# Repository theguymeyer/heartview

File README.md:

# Welcome to HeartView

A real-time testing system for pacemaker prototypes. 

The pacemaker project is a long standing challenge by Boston Scientific sponsored by McMaster University's Center for Software Certification -> [More](http://sqrl.mcmaster.ca/pacemaker.htm). This repo is the open-source (GPLv3) code base for the HeartView Testing GUI, embedded development files, and design files for the hardware and electrical systems. Even more info [here](https://guymeyer.me/project/heartview).

## Directory

HeartView Documentation -> https://github.com/theguymeyer/heartview/blob/master/course_dev/documentation/heartview_explained/intro_to_heartview.pdf

MacOS Executeable for HeartView -> https://github.com/theguymeyer/heartview/tree/master/course_dev/ui-HeartView/mac/exe

Windows Executeable for HeartView -> https://github.com/theguymeyer/heartview/tree/master/course_dev/ui-HeartView/win/exe

Nucleo Embedded Codebase -> https://github.com/theguymeyer/heartview/tree/master/course_dev/shield_nucleo_rev0/CubeMX

PCB Build Packages -> https://github.com/theguymeyer/heartview/tree/master/course_dev/Production/build

Heart Shield Design (Nucleo) -> https://github.com/theguymeyer/heartview/tree/master/course_dev/shield_nucleo_rev0

Pacemaker Shield Design -> https://github.com/theguymeyer/heartview/tree/master/course_dev/shield_pacemaker

Mechanical Design (casing) -> https://github.com/theguymeyer/heartview/tree/master/course_dev/casing/rev0

Testing Files -> https://github.com/theguymeyer/heartview/tree/master/course_dev/testing

## How to get involved

We invite you to contribute and help build a robust way to learn about pacemakers in a fun and engaging way. Reach out to the McSCert Research Group at McMaster Univeristy or get in touch view GitHub.

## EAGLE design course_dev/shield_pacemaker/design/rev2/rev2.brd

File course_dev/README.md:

# Pacemaker Project with Dedicated Testing System

TODO

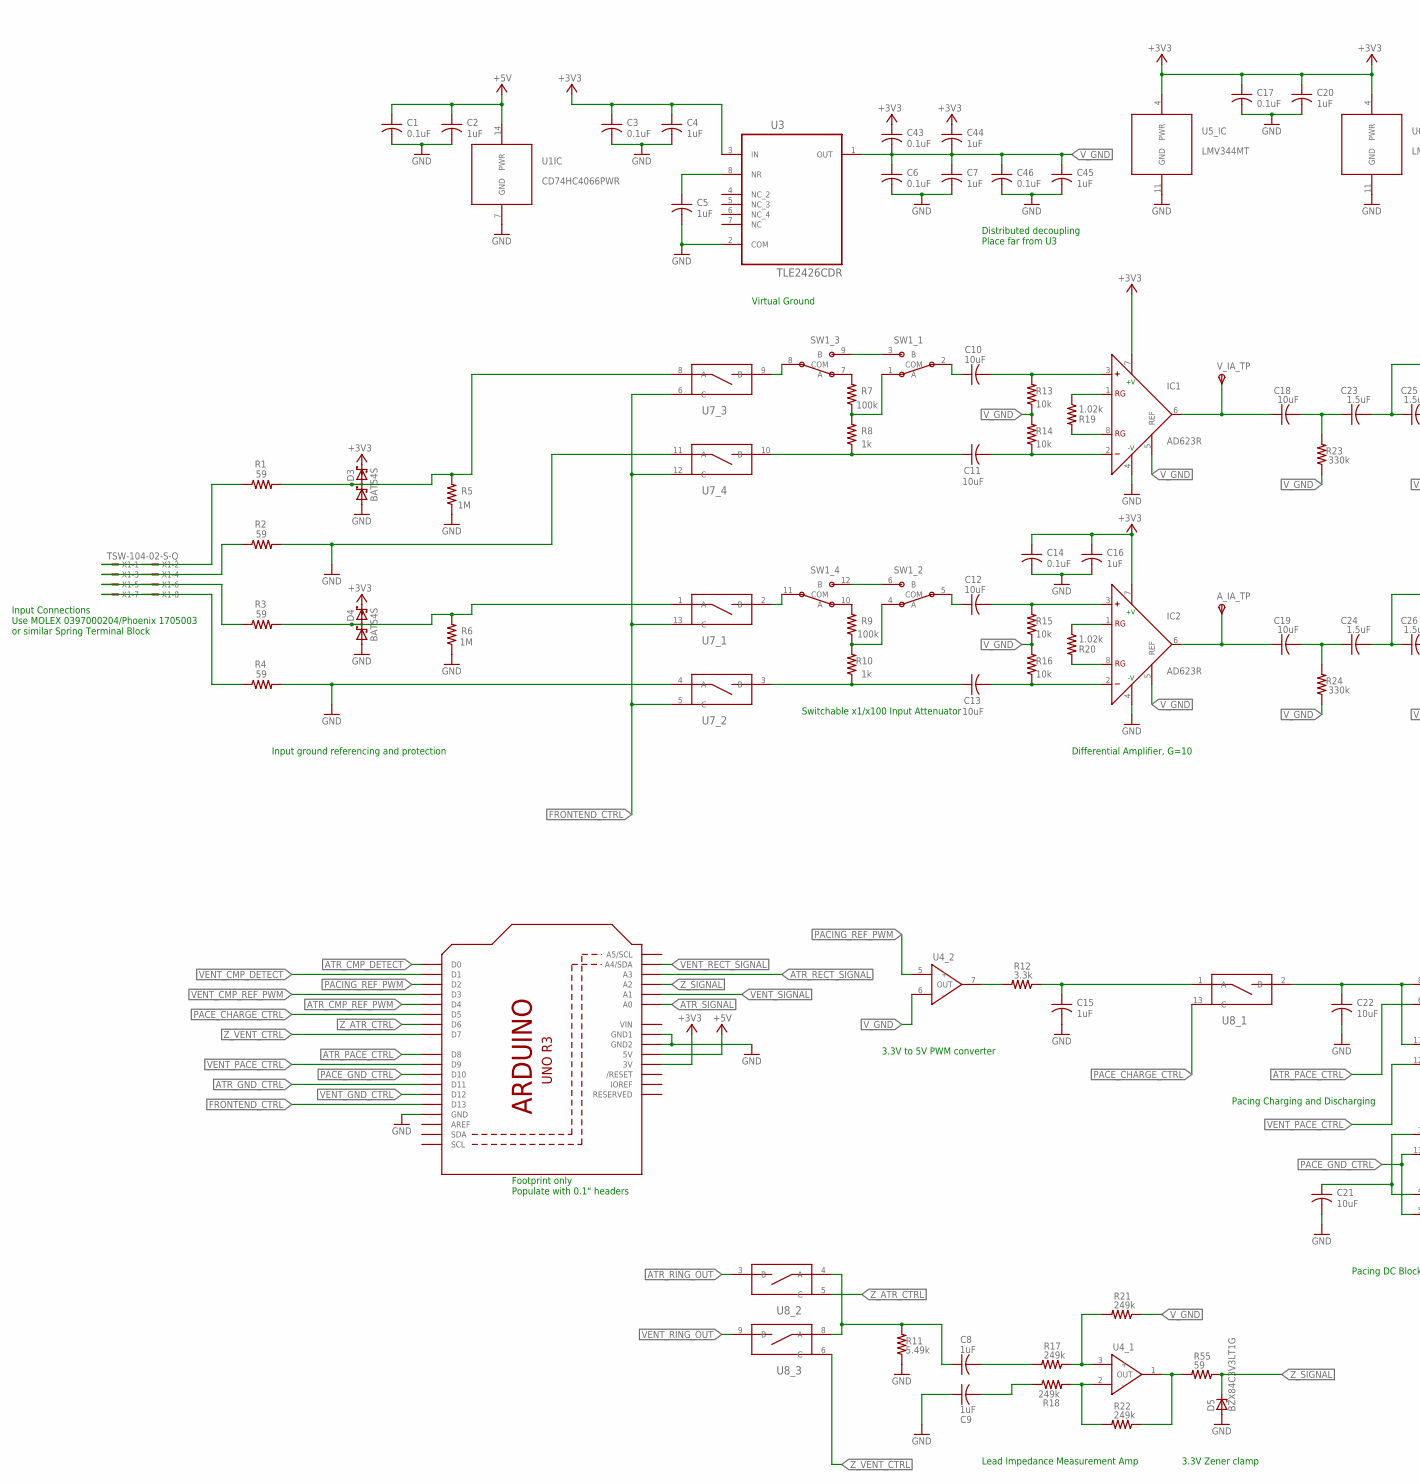
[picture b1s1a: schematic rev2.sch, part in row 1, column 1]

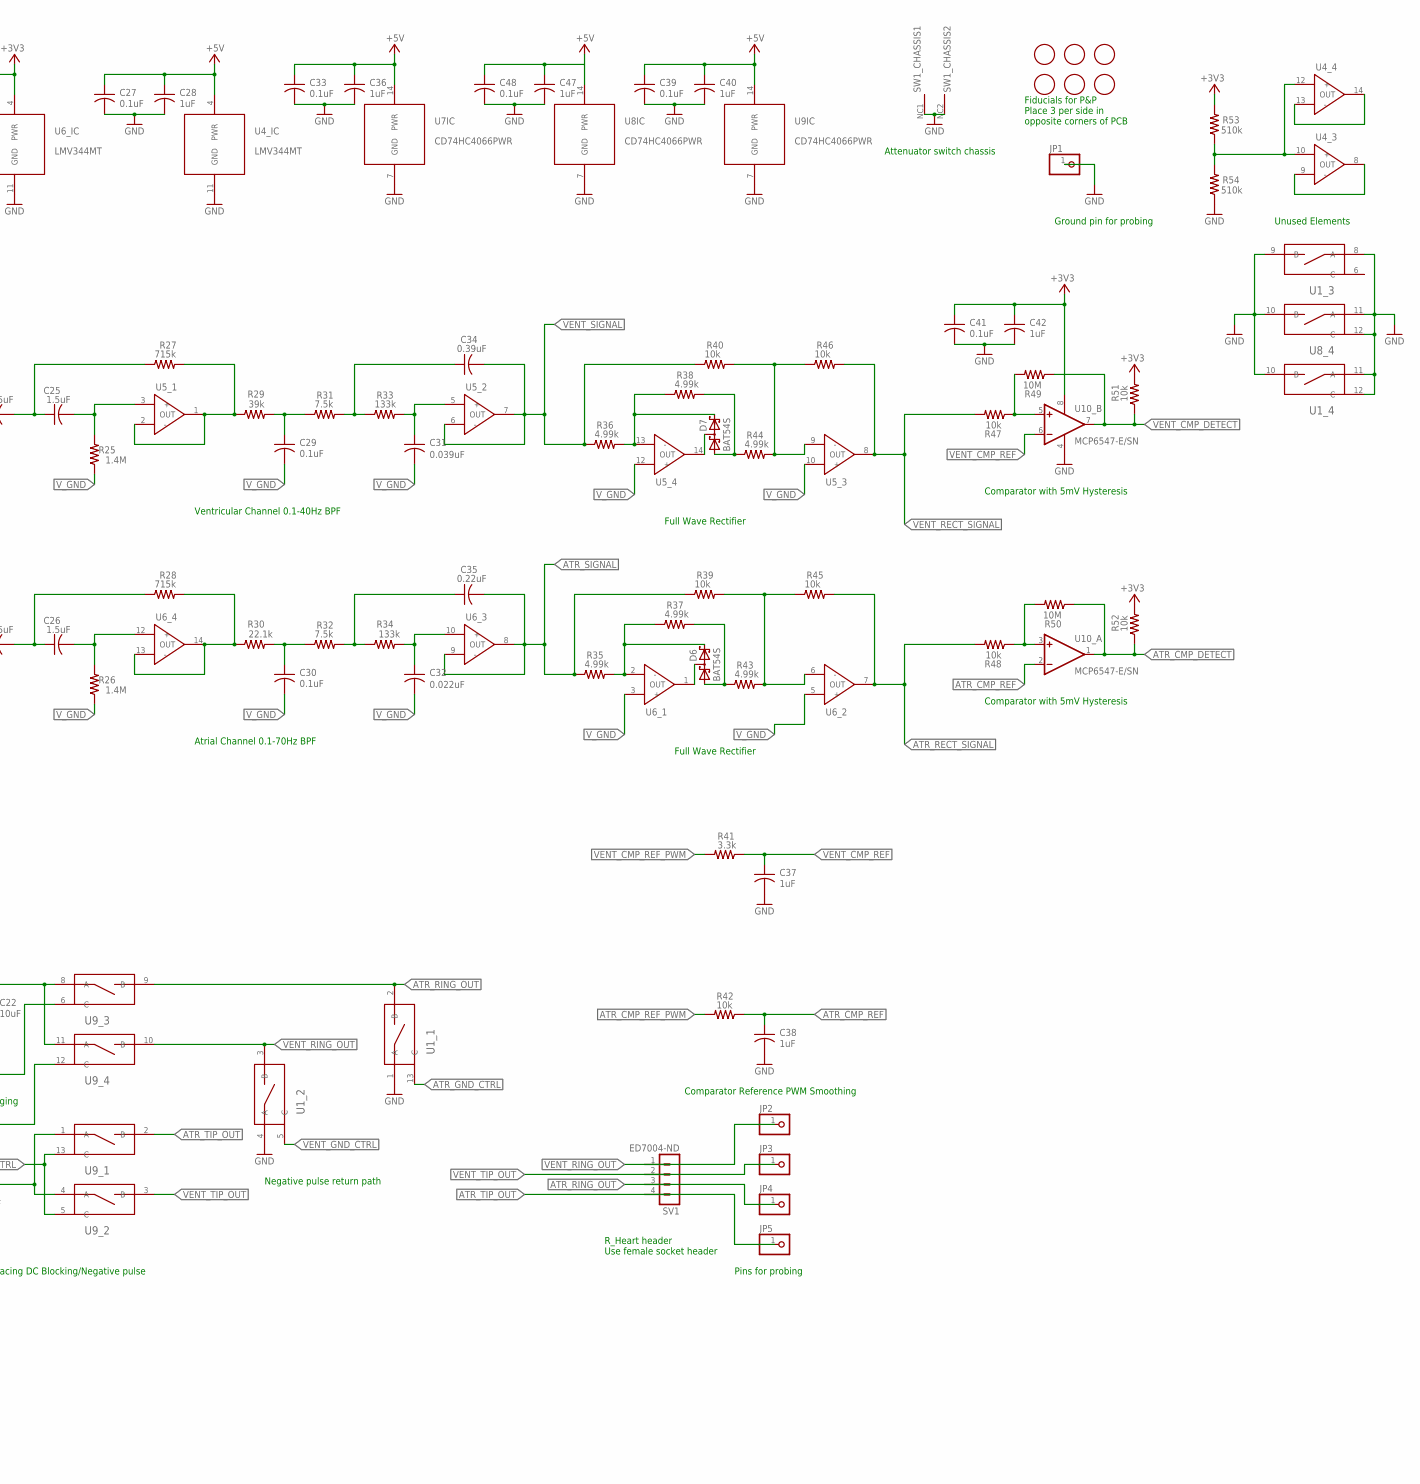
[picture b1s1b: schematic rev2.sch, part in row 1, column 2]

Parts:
A_IA_TP: TPSTP06R; TP06R
C1, C3, C6, C14, C17, C27, C29, C30, C33, C39, C41, C43, C46, C48: 0.1uF; C0805
C2, C4, C5, C7, C8, C9, C15, C16, C20, C28, C36, C37, C38, C40, C42, C44, C45, C47: 1uF; C0805
C10, C11, C12, C13, C18, C19, C21, C22: 10uF; C0805
C23, C24, C25, C26: 1.5uF; C0805
C31: 0.039uF; C0805
C32: 0.022uF; C0805
C34: 0.39uF; C0805
C35: 0.22uF; C0805
D3, D4, D6, D7: BAT54S; SOT23
D5: BZX84C3V3LT1G; SOT23
IC1, IC2: AD623R; SO8
JP1, JP2, JP3, JP4, JP5: PINHD-1X1; 1X01
R1, R2, R3, R4, R55: 59; R0805
R5, R6: 1M; R0805
R7, R9: 100k; R0805
R8, R10: 1k; R0805
R11: 5.49k; R0805
R12, R41: 3.3k; R0805
R13, R14, R15, R16, R39, R40, R42, R45, R46, R47, R48, R51, R52: 10k; R0805
R17, R18, R21, R22: 249k; R0805
R19, R20: 1.02k; R0805
R23, R24: 330k; R0805
R25, R26: 1.4M; R0805
R27, R28: 715k; R0805
R29: 39k; R0805
R30: 22.1k; R0805
R31, R32: 7.5k; R0805
R33, R34: 133k; R0805
R35, R36, R37, R38, R43, R44: 4.99k; R0805
R49, R50: 10M; R0805
R53, R54: 510k; R0805
SV1: ED7004-ND; MA04-1
SW1: EG4208; EG4208-PACKAGE
U1, U7, U8, U9: CD74HC4066PWR; SOP65P640X110-14N
U2: ARDUINOR3-DIMENSION; ARDUINOR3
U3: TLE2426CDR; SOIC127P600X175-8N
U4, U5, U6: LMV344MT; SOP65P640X110-14N
U10: MCP6547-E/SN; SOIC127P600X175-8N
U$1, U$2, U$3, U$4, U$5, U$6: FIDUCIAL; FIDUCIAL_1MM
V_IA_TP: TPSTP06R; TP06R
X1: TSW-104-02-S-Q

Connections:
+3V3: C3.1, C4.1, C14.1, C16.1, C17.1, C20.1, C41.1, C42.1, C43.1, C44.1, D3.2 (C2), D4.2 (C2), IC1.7 (+V), IC2.7 (+V), R51.2, R52.2, R53.2, U2.3V, U3.3 (IN), U5.4 (PWR), U6.4 (PWR), U10.8 (V+)
+5V: C1.1, C2.1, C27.1, C28.1, C33.1, C36.1, C39.1, C40.1, C47.1, C48.1, U1.14 (PWR), U2.5V, U4.4 (PWR), U7.14 (PWR), U8.14 (PWR), U9.14 (PWR)
ATR_CMP_DETECT: R50.1, R52.1, U2.D0, U10.1 (OUT)
ATR_CMP_REF: C38.1, R42.1, U10.2 (-IN)
ATR_CMP_REF_PWM: R42.2, U2.D4
ATR_GND_CTRL: U1.13 (C), U2.D11
ATR_PACE_CTRL: U2.D8, U9.6 (C)
ATR_RECT_SIGNAL: R45.2, R48.2, U2.A3, U6.7 (OUT)
ATR_RING: D4.3 (C1A2), R3.2, R6.2, U7.1 (A)
ATR_RING_OUT: JP4.1, SV1.3, U1.2 (B), U8.3 (B), U9.9 (B)
ATR_SIGNAL: C35.2, R35.1, R39.1, U2.A0, U6.8 (OUT), U6.9 (-)
ATR_TIP_OUT: JP5.1, SV1.4, U9.2 (B)
FRONTEND_CTRL: U2.D13, U7.5 (C), U7.6 (C), U7.12 (C), U7.13 (C)
GND: C1.2, C2.2, C3.2, C4.2, C5.2, C6.2, C7.2, C9.1, C14.2, C15.2, C16.2, C17.2, C20.2, C21.2, C22.2, C27.2, C28.2, C33.2, C36.2, C37.2, C38.2, C39.2, C40.2, C41.2, C42.2, C45.2, C46.2, C47.2, C48.2, D3.1 (A1), D4.1 (A1), D5.1 (A), IC1.4 (-V), IC2.4 (-V), JP1.1, R2.2, R4.2, R5.1, R6.1, R11.1, R54.1, SW1.NC1 (V-), SW1.NC2 (V-), U1.1 (A), U1.4 (A), U1.7 (GND), U1.8 (A), U1.9 (B), U1.10 (B), U1.11 (A), U1.12 (C), U2.GND, U2.GND1, U2.GND2, U3.2 (COM), U4.11 (GND), U5.11 (GND), U6.11 (GND), U7.4 (A), U7.7 (GND), U7.11 (A), U8.7 (GND), U8.10 (B), U8.11 (A), U8.12 (C), U9.7 (GND), U10.4 (V-)
unnamed: C10.2, IC1.3 (+), R13.2
unnamed: C11.2, IC1.2 (-), R14.1
unnamed: C18.1, IC1.6 (OUT), V_IA_TP.TP
unnamed: IC1.1 (RG), R19.1
unnamed: R7.2, SW1.7 (A)
unnamed: C18.2, C23.1, R23.2
unnamed: C23.2, C25.1, R27.1
unnamed: C11.1, R8.1, U7.10 (B)
unnamed: C13.2, IC2.2 (-), R16.1
unnamed: C29.1, R29.2, R31.1
unnamed: C34.1, R31.2, R33.1
unnamed: C13.1, R10.1, U7.3 (B)
unnamed: D6.2 (C2), R35.2, R37.1, U6.2 (-)
unnamed: R9.2, SW1.10 (A)
unnamed: IC2.1 (RG), R20.1
unnamed: IC2.8 (RG), R20.2
unnamed: C19.2, C24.1, R24.2
unnamed: D6.3 (C1A2), U6.1 (OUT)
unnamed: IC1.8 (RG), R19.2
unnamed: C12.2, IC2.3 (+), R15.2
unnamed: C15.1, R12.1, U8.1 (A)
unnamed: C21.1, U9.1 (A), U9.4 (A)
unnamed: R22.1, R55.2, U4.1 (OUT)
unnamed: D7.3 (C1A2), U5.14 (OUT)
unnamed: R28.2, R30.1, U6.13 (-), U6.14 (OUT)
unnamed: SW1.6 (B), SW1.12 (B)
unnamed: C24.2, C26.1, R28.1
unnamed: C22.1, U8.2 (B), U9.8 (A), U9.11 (A)
unnamed: C25.2, R25.2, U5.3 (+)
unnamed: R27.2, R29.1, U5.1 (OUT), U5.2 (-)
unnamed: C5.1, U3.8 (NR)
unnamed: C31.1, R33.2, U5.5 (+)
unnamed: C30.1, R30.2, R32.1
unnamed: R48.1, R50.2, U10.3 (+IN)
unnamed: C35.1, R32.2, R34.1
unnamed: D6.1 (A1), R37.2, R43.1
unnamed: C26.2, R26.2, U6.12 (+)
unnamed: R47.1, R49.2, U10.5 (+IN)
unnamed: C32.1, R34.2, U6.10 (+)
unnamed: R39.2, R43.2, R45.1, U6.6 (-)
unnamed: SW1.3 (B), SW1.9 (B)
unnamed: C8.1, R11.2, U8.4 (A), U8.8 (A)
unnamed: A_IA_TP.TP, C19.1, IC2.6 (OUT)
unnamed: U4.8 (OUT), U4.9 (-)
unnamed: R12.2, U4.7 (OUT)
unnamed: R17.1, R21.2, U4.3 (+)
unnamed: R18.2, R22.2, U4.2 (-)
unnamed: C9.2, R18.1
unnamed: C8.2, R17.2
unnamed: U4.13 (-), U4.14 (OUT)
unnamed: R53.1, R54.2, U4.10 (+), U4.12 (+)
unnamed: R4.1, X1.7, X1.8
unnamed: R2.1, X1.3, X1.4
unnamed: R3.1, X1.5, X1.6
unnamed: R7.1, R8.2, SW1.1 (A)
unnamed: R1.1, X1.1, X1.2
unnamed: SW1.8 (COM), U7.9 (B)
unnamed: SW1.11 (COM), U7.2 (B)
unnamed: R9.1, R10.2, SW1.4 (A)
unnamed: D7.2 (C2), R36.2, R38.1, U5.13 (-)
unnamed: C12.1, SW1.5 (COM)
unnamed: C10.1, SW1.2 (COM)
unnamed: D7.1 (A1), R38.2, R44.1
unnamed: R40.2, R44.2, R46.1, U5.9 (-)
PACE_CHARGE_CTRL: U2.D5, U8.13 (C)
PACE_GND_CTRL: U2.D10, U9.5 (C), U9.13 (C)
PACING_REF_PWM: U2.D2, U4.5 (+)
VENT_CMP_DETECT: R49.1, R51.1, U2.D1, U10.7 (OUT)
VENT_CMP_REF: C37.1, R41.1, U10.6 (-IN)
VENT_CMP_REF_PWM: R41.2, U2.D3
VENT_GND_CTRL: U1.5 (C), U2.D12
VENT_PACE_CTRL: U2.D9, U9.12 (C)
VENT_RECT_SIGNAL: R46.2, R47.2, U2.A4 (A4/SDA), U5.8 (OUT)
VENT_RING: D3.3 (C1A2), R1.2, R5.2, U7.8 (A)
VENT_RING_OUT: JP2.1, SV1.1, U1.3 (B), U8.9 (B), U9.10 (B)
VENT_SIGNAL: C34.2, R36.1, R40.1, U2.A1, U5.6 (-), U5.7 (OUT)
VENT_TIP_OUT: JP3.1, SV1.2, U9.3 (B)
VIN: U2.VIN
V_GND: C6.1, C7.1, C29.2, C30.2, C31.2, C32.2, C43.2, C44.2, C45.1, C46.1, IC1.5 (REF), IC2.5 (REF), R13.1, R14.2, R15.1, R16.2, R21.1, R23.1, R24.1, R25.1, R26.1, U3.1 (OUT), U4.6 (-), U5.10 (+), U5.12 (+), U6.3 (+), U6.5 (+)
Z_ATR_CTRL: U2.D6, U8.5 (C)
Z_SIGNAL: D5.3 (C), R55.1, U2.A2
Z_VENT_CTRL: U2.D7, U8.6 (C)

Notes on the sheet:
Ventricular Channel 0.1-40Hz BPF
Atrial Channel 0.1-70Hz BPF
Pacing Charging and Discharging
Unused Elements
Lead Impedance Measurement Amp
Pacing DC Blocking/Negative pulse
Comparator with 5mV Hysteresis
Comparator Reference PWM Smoothing
Footprint only Populate with 0.1" headers
Differential Amplifier, G=10
3.3V to 5V PWM converter
Input ground referencing and protection
Switchable x1/x100 Input Attenuator
R_Heart header Use female socket header
Negative pulse return path
Full Wave Rectifier
Virtual Ground
Distributed decoupling Place far from U3
Input Connections Use MOLEX 0397000204/Phoenix 1705003 or similar Spring Terminal Block
Pins for probing
Fiducials for P&P Place 3 per side in opposite corners of PCB
Ground pin for probing
Attenuator switch chassis
3.3V Zener clamp

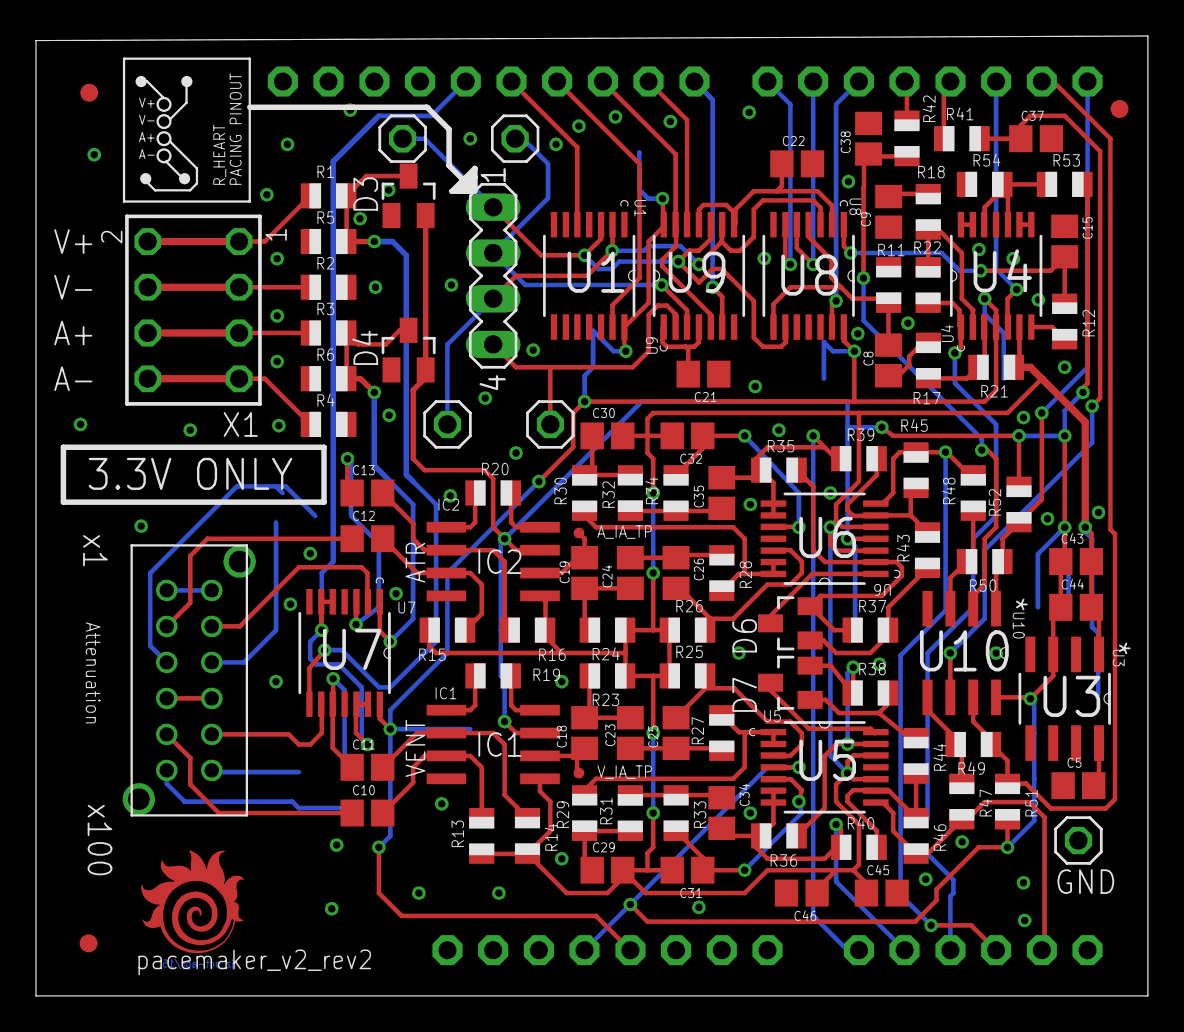
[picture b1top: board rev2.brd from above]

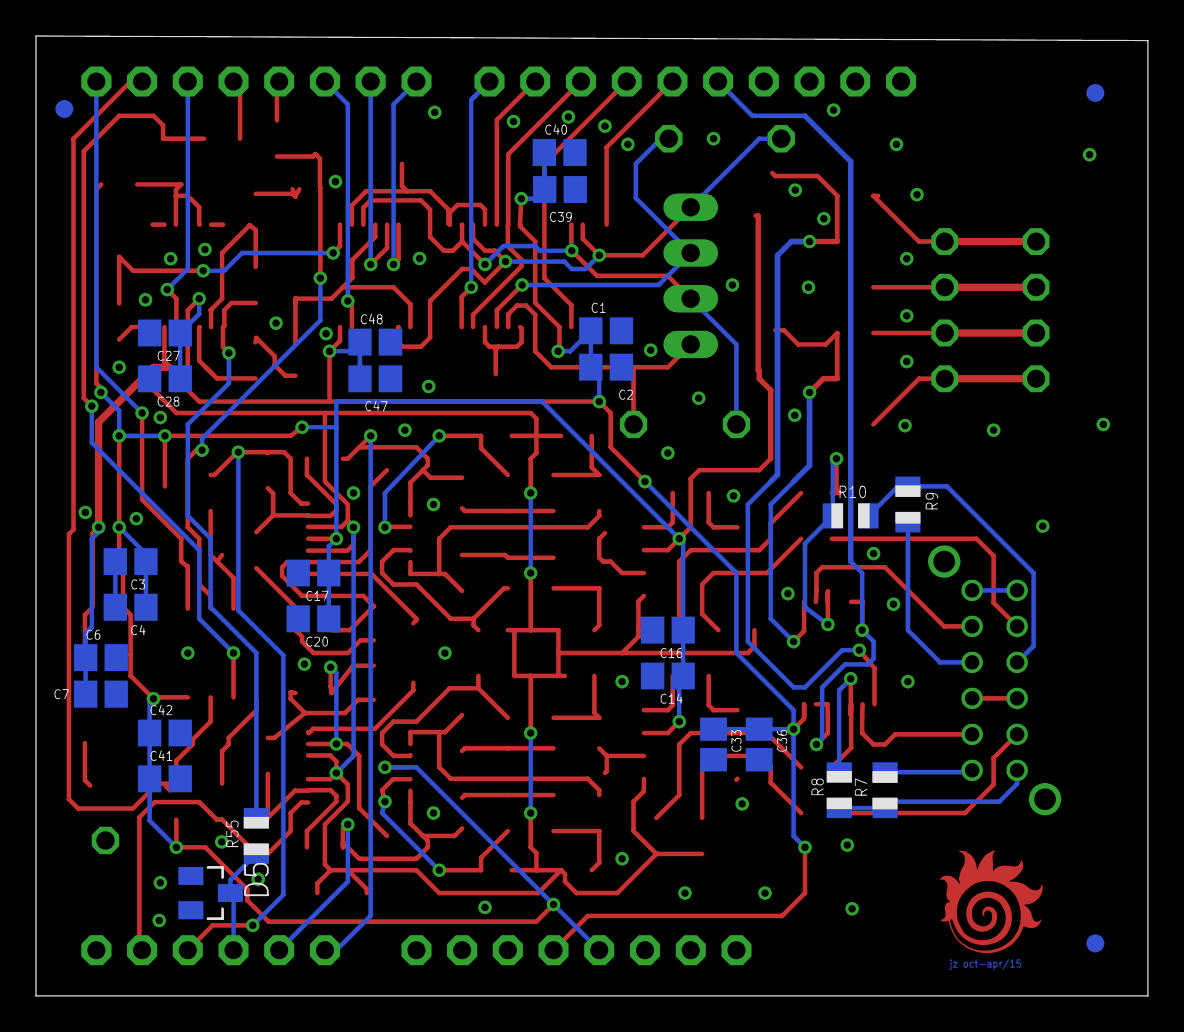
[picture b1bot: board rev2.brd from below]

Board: 2 copper layers, 61.8 x 53.3 mm, 137 parts (29 on the bottom side), 95 nets.

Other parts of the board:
U$7: FIREBALL

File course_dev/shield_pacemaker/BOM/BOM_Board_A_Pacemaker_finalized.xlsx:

BOM - Board A (Pacemaker)
# | Designator | Quantity | Comment | Value | Footprint | Description | Manufacturer | Price | Total Price
1 | C32 | 1 | CAP CER 0.022UF 50V X7R 0805 | C0805C223K5RACTU | 0805 | SMD/SMT 50V 0.022uF X7R 0805 10% | KEMET | 0.15 | 0.15
2 | C31 | 1 | CAP CER 0.039UF 50V X7R 0805 | C0805C393K5RACTU | 0805 | SMD/SMT 50V 0.039uF X7R 0805 10% | KEMET | 0.34 | 0.34
3 | C1, C3, C6, C14, C17, C27, C29, C30, C33, C39, C41, C43, C46, C48 | 14 | CAP CER 0.1UF 50V X7R 0805 | C0805C104J5RACTU | 0805 | SMD/SMT 50V 0.1uF X7R 0805 5% | KEMET | 0.195 | 2.73
4 | C35 | 1 | CAP CER 0.22UF 16V X7R 0805 | C0805C224K4RACTU | 0805 | SMD/SMT 16V 0.22uF X7R 0805 10% | KEMET | 0.3 | 0.3
5 | C34 | 1 | CAP CER 0.39UF 50V X7R 0805 | C0805X394K5RACTU | 0805 | SMD/SMT 50V 0.39uF X7R 0805 10% | KEMET | 0.98 | 0.98
6 | R19, R20 | 2 | RES SMD 1.02K OHM 1% 1/8W 0805 | ERJ-6ENF1021V | 0805 | SMD 0805 1.02Kohms 1% | Panasonic Electronic Components | 0.16 | 0.32
7 | R25, R26 | 2 | RES SMD 1.4M OHM 1% 1/8W 0805 | ERJ-6ENF1404V | 0805 | SMD 0805 1.4Mohms 1% | Panasonic Electronic Components | 0.16 | 0.32
8 | C23, C24, C25, C26 | 4 | CAP CER 1.5UF 50V X7R 0805 | C2012X7R1H155K125AC | 0805 | SMD/SMT 0805 50V 1.5uF X7R 10% | TDK Corporation | 1.09 | 4.36
9 | R7, R9 | 2 | RES SMD 100K OHM 1% 1/8W 0805 | ERJ-6ENF1003V | 0805 | SMD 0805 100Kohms 1% | Panasonic Electronic Components | 0.16 | 0.32
10 | R49, R50 | 2 | RES SMD 10M OHM 1% 1/8W 0805 | CRCW080510M0FKEB | 0805 | SMD 1/8watt 10Mohms 1% | Vishay Dale | 0.16 | 0.32
11 | R13, R14, R15, R16, R39, R40, R42, R45, R46, R47, R48, R51, R52 | 13 | RES SMD 10K OHM 1% 1/8W 0805 | ERJ-6ENF1002V | 0805 | SMD 0805 10Kohms 1% | Panasonic Electronic Components | 0.114 | 1.482
12 | C10, C11, C12, C13, C18, C19, C21, C22 | 8 | CAP CER 10UF 10V X5R 0805 | CL21A106KPFNNWE | 0805 | SMD/SMT 10V 10uF X7R 0805 10% | Samsung Electro-Mechanics | 0.27 | 2.16
13 | R33, R34 | 2 | RES SMD 133K OHM 1% 1/8W 0805 | ERJ-6ENF1333V | 0805 | SMD 0805 133Kohms 1% | Panasonic Electronic Components | 0.16 | 0.32
14 | R5, R6 | 2 | RES SMD 1M OHM 1% 1/8W 0805 | ERJ-6ENF1004V | 0805 | SMD 0805 1Mohms 1% Tol | Panasonic Electronic Components | 0.16 | 0.32
15 | R8, R10 | 2 | RES SMD 1K OHM 1% 1/8W 0805 | ERJ-6ENF1001V | 0805 | SMD 0805 1Kohms 1% | Panasonic Electronic Components | 0.16 | 0.32
16 | C2, C4, C5, C7, C8, C9, C15, C16, C20, C28, C36, C37, C38, C40, C42, C44, C45, 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 | 18 | CAP CER 1UF 16V X5R 0805 | C0805C105K4PACTU | 0805 | SMD/SMT 16V 1uF X5R 0805 10% | KEMET | 0.231 | 4.158
17 | R30 | 1 | RES SMD 22.1K OHM 1% 1/8W 0805 | ERJ-6ENF2212V | 0805 | SMD 0805 22.1Kohms 1% | Panasonic Electronic Components | 0.16 | 0.16
18 | R17, R18, R21, R22 | 4 | RES SMD 249K OHM 1% 1/8W 0805 | ERJ-6ENF2493V | 0805 | SMD 0805 249Kohms 1% | Panasonic Electronic Components | 0.16 | 0.64
19 | R12, R41 | 2 | RES SMD 3.3K OHM 1% 1/8W 0805 | ERJ-6ENF3301V | 0805 | SMD 0805 3.3Kohms 1% | Panasonic Electronic Components | 0.16 | 0.32
20 | R23, R24 | 2 | RES SMD 330K OHM 1% 1/8W 0805 | ERJ-6ENF3303V | 0805 | SMD 0805 330Kohms 1% | Panasonic Electronic Components | 0.16 | 0.32
21 | R29 | 1 | RES SMD 39K OHM 1% 1/8W 0805 | ERJ-6ENF3902V | 0805 | SMD 0805 39Kohms 1% | Panasonic Electronic Components | 0.16 | 0.16
22 | R35, R36, R37, R38, R43, R44 | 6 | RES SMD 4.99K OHM 1% 1/8W 0805 | ERJ-6ENF4991V | 0805 | SMD 0805 4.99Kohms 1% | Panasonic Electronic Components | 0.16 | 0.96
23 | R11 | 1 | RES SMD 5.49K OHM 1% 1/8W 0805 | ERJ-6ENF5491V | 0805 | SMD 0805 5.49Kohms 1% | Panasonic Electronic Components | 0.16 | 0.16
24 | R53, R54 | 2 | RES SMD 510K OHM 1% 1/8W 0805 | ERJ-6ENF5103V | 0805 | SMD 0805 510Kohms 1% | Panasonic Electronic Components | 0.16 | 0.32
25 | R1, R2, R3, R4, R55 | 5 | RES SMD 59 OHM 1% 1/8W 0805 | ERJ-6ENF59R0V | 0805 | SMD 0805 59.0ohms 1% Tol | Panasonic Electronic Components | 0.16 | 0.8
26 | R31, R32 | 2 | RES SMD 7.5K OHM 1% 1/8W 0805 | ERJ-6ENF7501V | 0805 | SMD 0805 7.5Kohms 1% | Panasonic Electronic Components | 0.16 | 0.32
27 | R27, R28 | 2 | RES SMD 715K OHM 1% 1/8W 0805 | ERJ-6ENF7153V | 0805 | SMD 0805 715Kohms 1% | Panasonic Electronic Components | 0.16 | 0.32
28 | D3, D4, D6, D7 | 4 | DIODE ARRAY SCHOTTKY 30V SOT23 | BAT54S,215 | SOT-23-3 | SCHOTTKY 30V DUAL | Nexperia USA Inc. | 0.21 | 0.84
29 | D5 | 1 | DIODE ZENER 3.3V 225MW SOT23-3 | BZX84C3V3LT1G | SOT-23-3 | DIODE ZENER 3.3V 225MW SOT23-3 | ON Semiconductor | 0.19 | 0.19
30 | U1, U7, U8, U9 | 4 | IC SWITCH QUAD 1X2 14TSSOP | CD74HC4066PWR | TSSOP-14 | IC SWITCH QUAD 1X2 14TSSOP | Texas Instruments | 0.86 | 3.44
31 | SW1 | 1 | SWITCH SLIDE 4PDT 200MA 30V | EG4208 |  | SWITCH SLIDE 4PDT 200MA 30V | E-Switch | 1.95 | 1.95
32 | U4, U5, U6 | 3 | IC OPAMP GP 4 CIRCUIT 14TSSOP | LMV774MT/NOPB | TSSOP-14 | IC OPAMP GP 4 CIRCUIT 14TSSOP | Texas Instruments | 4.45 | 13.35
33 | U10 | 1 | IC COMP 1.6V DUAL O-D 8SOIC | MCP6547-E/SN | SOIC-8 | IC COMP 1.6V DUAL O-D 8SOIC | Microchip Technology | 0.91 | 0.91
34 | U3 | 1 | IC VREF GND REF 20V 1% 8SOIC | TLE2426CDR | SOIC-8 | IC VREF GND REF 20V 1% 8SOIC | Texas Instruments | 3.29 | 3.29
35 | PACEOUT | 1 | 55932-0430 | 55932-0430 | B4B-PH-K-S | CONN HEADER VERT 4POS 2MM | Molex | 0.31 | 0.31
36 | HRTIN | 1 | 35312-0460 | 35312-0460 | B4B-XH-A | CONN HEADER VERT 4POS 2.5MM | Molex | 0.36 | 0.36
37 | J2 | 1 | PREC010SFAN-RC | PREC010SFAN-RC |  | CONN HEADER VERT 10POS 2.54MM | Sullins Connector Solutions | 0.258 | 0.258
38 | J3, J4 | 2 | PREC008SFAN-RC | PREC008SFAN-RC |  | CONN HEADER VERT 8POS 2.54MM | Sullins Connector Solutions | 0.2065 | 0.413
39 | J1 | 1 | PREC006SFAN-RC | PREC006SFAN-RC |  | CONN HEADER VERT 6POS 2.54MM | Sullins Connector Solutions | 0.1548 | 0.1548
40 | IC1, IC2 | 2 | IC INST AMP 1 CIRCUIT 8SOIC | AD8226ARZ-R7 | 8SOIC | IC INST AMP 1 CIRCUIT 8SOIC | Analog Devices Inc. | 4.8 | 9.6
41 | JP1 | 0 | Test Point |  |  |  |  | 0 | 0
42 | JP2 | 0 | Test Point |  |  |  |  | 0 | 0
43 | JP3 | 0 | Test Point |  |  |  |  | 0 | 0
44 | JP4 | 0 | Test Point |  |  |  |  | 0 | 0
45 | JP5 | 0 | Test Point |  |  |  |  | 0 | 0
46 | A_IA_TP | 0 | Test Point |  |  |  |  | 0 | 0
47 | V_IA_TP | 0 | Test Point |  |  |  |  | 0 | 0
 |  |  |  |  |  |  |  | Total Price | 53.3058

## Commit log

2020-07-17 add .gitignore
2020-07-20 ignore ds_store
2020-07-20 add HeartView
2020-07-20 more .gitignore
2020-07-20 course_dev README.md
2020-07-20 pacemaker files
2020-07-20 add shields files
2020-07-20 pyinstaller docs
2020-07-20 mechanical casing
2020-07-20 production
2020-07-20 updated BOM nucleo
2020-07-21 10ms and 5ms PW
2020-07-21 updated BOM
2020-07-22 working spec file
2020-07-22 updates to README
2020-07-22 track dist
2020-07-22 dist .ip
2020-07-22 correction: dist .zip
2020-07-22 HV spec for windows
2020-07-27 build package zip
2020-07-28 init info.plist
2020-07-28 bash script for fast compilation
2020-07-29 edit info.plist
2020-07-29 edit bundler script
2020-07-29 signed app v0
2020-07-29 recent bulid info
2020-07-29 add README gen app + codesigning + deployment
2020-07-29 add --deep
2020-07-29 add block for manual
2020-07-29 correct block for manual
2020-07-30 change mainwindow title
2020-07-30 add manual to README
2020-07-30 add deploy folder + macos v0
2020-07-30 add to git lfs
2020-07-30 removed hv zip
2020-07-30 recent build
2020-07-30 modify mainwindow for windows
2020-07-30 windows bundler init
2020-07-30 windows spec file
2020-07-30 windows exe
2020-07-30 add mac folder
2020-07-30 add win folder
2020-07-30 track exe
2020-07-30 remove old dir
2020-07-30 add imgs lfs
2020-07-30 pulled
2020-07-30 resolve img
2020-07-30 readme init
2020-07-30 spec changes
2020-07-30 img linsk
2020-07-30 add img links
2020-07-30 changed name
2020-07-30 working img links
2020-07-30 .gitattr
2020-07-30 lfs track win10
2020-07-30 img links
2020-07-30 .toc + .dot >> gitignore
2020-07-30 hv win10 exe
2020-07-30 batch file improvs
2020-07-30 win README
2020-07-30 spec img links
2020-07-30 remove bad zip
2020-07-31 label updates
2020-07-31 remove button toggle
2020-07-31 fix plots to 5V
2020-07-31 correct plot scaling
2020-07-31 add tutorial window
2020-07-31 cleanup
2020-07-31 add tutorial file desc
2020-07-31 text corrections
2020-07-31 updated dist
2020-08-04 move libs
2020-08-04 update spec files
2020-08-04 move main files
2020-08-06 add gitignore docs
2020-08-06 init heartview explained doc
2020-08-06 add pdf to gitignore
2020-08-10 hack: recover from too much pending data
2020-08-10 documentation
2020-08-10 docs for hack
2020-08-10 HeartView 1.0
2020-08-10 add tutorial
2020-08-10 diplay tutorial
2020-08-10 remove librayr
2020-08-10 HeartView 1.0 (win10)
2020-08-11 HeartView 1.0.0 (win10)
2020-08-11 create LICENSE
    LIcensed under the GPLv3 copyleft agreement
    Guy Meyer (Aug 11 2020)
2020-08-11 change plist to heartview
2020-08-11 update serial
2020-08-11 rm win base lib
2020-08-12 update gitignore
2020-08-12 HeartView 1.0.0 (macOS 10.14 Mojave+)
2020-08-28 updated HeartView win10
2020-08-28 new docs
2020-08-28 update pcb design
2020-08-28 connector spec
2020-08-28 test spec
2020-09-08 mod gitignore
2020-09-08 add production files
2020-09-08 hv explained
2020-09-08 updates to HV UI
2020-09-08 add shield fab docs
2020-09-09 heartview pdf
2020-09-10 Add testing files
2020-11-18 add cubemx to gitignore
2020-11-18 add embedded code + docs
2020-11-18 main README
2020-11-18 fix spacing
2021-03-26 Bump pyyaml from 5.3.1 to 5.4 in /course_dev/testing
    Bumps [pyyaml](https://github.com/yaml/pyyaml) from 5.3.1 to 5.4.
    - [Release notes](https://github.com/yaml/pyyaml/releases)
    - [Changelog](https://github.com/yaml/pyyaml/blob/master/CHANGES)
    - [Commits](https://github.com/yaml/pyyaml/compare/5.3.1...5.4)
